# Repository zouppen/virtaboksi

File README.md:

# Virtaboksi

Virtaboksi is a multi-purpose 3-channel common-earth power switch,
rating 12–48 VDC, 20 A. It has multiple operating modes:

* **Home/away switch** supporting three individual groups and is optimized
  for solar energy off-grid applications.

* **Water pump controller** with pressure sensor input and control for
  combined submersible and pressure pump system. Additionally, a
  throw-over switching capability to drop loads while pumping.

* Generic **Modbus RTU server** (slave) with 3 solid-state "coils", 3 digital
  outputs, and 4 digital inputs.

In the picture above the Powerpole connector colors are incorrect. Red
is used for inputs and black for outputs. In a real product, the three
groups have different colors: red, yellow and blue.

## Design principles

* **Flexible voltage** options; 10–34 V input on first group, 10–60 V on
  second and third group.
* **High current** support. With passive cooling, 20 A loads can be
  controlled. MOSFETs are capable of switching over 100 A continuous
  current in case where cooling and PCB traces are reinforced.
* **Small** size: Thanks to transistor control, the size is way smaller than for
  three contactors of similar rating.
* **Low losses**: Internal resistance <10mΩ.
* **Rugged**: All digital I/O ports are short-circuit, reverse voltage and
  surge protected.
* **Power saving**: When loads are off, the power consumption is minimal,
  less than 5mW, allowing it to be left powered on over dark winters.
* **Hacker friendly**: You can create your own firmware for the STM8
  microcontroller, allowing real-time and stand-alone control of your
  loads and connectivity to other peripherals up to **1 km** distance
  over RS-485.

## Operating modes

### Home/away mode

Status: 💚 **Functional**

This unit provides *priority* output on OUT1 when the switch is in
either *home* or *away* position. *Home* controls OUT2 and OUT3 groups
and can be used to control two separate voltages as long as they have
a common ground.

An example use case is a solar off-grid system with two 12V batteries
in series providing 24 volts, plus 12 volts generated from 24V using a
step-down DC converter. DC converter is not included in the package.

In that case this switch can be used to turn the loads partially while
being away, such as keeping refrigerator running but turning off
lights while not present. When using a DC converter, its input is connected
OUT1 its output (12V) to IN3.

Maximum voltage in IN1 is 34 VDC. The limitation comes from the
internal power supply. In case you want to use higher voltages in IN1,
cut the trace F1 on the bottom of this board and power the system
directly from a regulated 3.3 VDC supply via the terminals.

IN2 and IN3 are rated for 60 volts maximum, making it possible to
control 48V nominal voltage loads. Minimum voltage for all groups is
about 10 volts. Under 10 volts, MOSFET control becomes unreliable.

#### How to connect

In home/away mode, when I1 is shorted to the ground, the oprating mode
is *away*. When I2 is shorted, the mode is *home*. If both connectors
are open, operating mode is *off*.

Optionally, LED anodes can be connected directly to O1 and O2. They
represent home and away operating modes, in that order. There is a
current limiter controllable by R1 to limit the maximum current of
O1...O3 to about 15 mA by default, so series resistors are not needed.

If your solar controller has a low battery condition relay, it can be
connected to I3. When the input is high, the system is forced to off mode,
ignoring the state of home/away switch.

I4 is not used in this mode.

### Water pump controller mode

Status: 🔬 **Hardware OK**

Hardware is capable, but no firmware support yet.

### Modbus RTU server mode

Status: 🔬 **Hardware OK**

RS-485 hardware is tested and some firmware tests performed, but no
Modbus implementation exists yet.

## Building firmware

To build firmware, you need CMake and sdcc. The preparations are very
standard CMake stuff. In `firmware` subdirectory, run:

```sh
mkdir build
cd build
cmake ..
```

And then, `make` compiles it. Alternatively, `make upload` to compile
and flash.

## License

The firmware is free software: you can redistribute it and/or modify
it under the terms of the GNU Affero General Public License as
published by the Free Software Foundation, either version 3 of the
License, or (at your option) any later version.

The hardware is provided as source-available: The schematics and PCB
layout are provided for reference only. The files can be freely
distributed without limitations but no derivative works are allowed
without a permission from the copyright holders.

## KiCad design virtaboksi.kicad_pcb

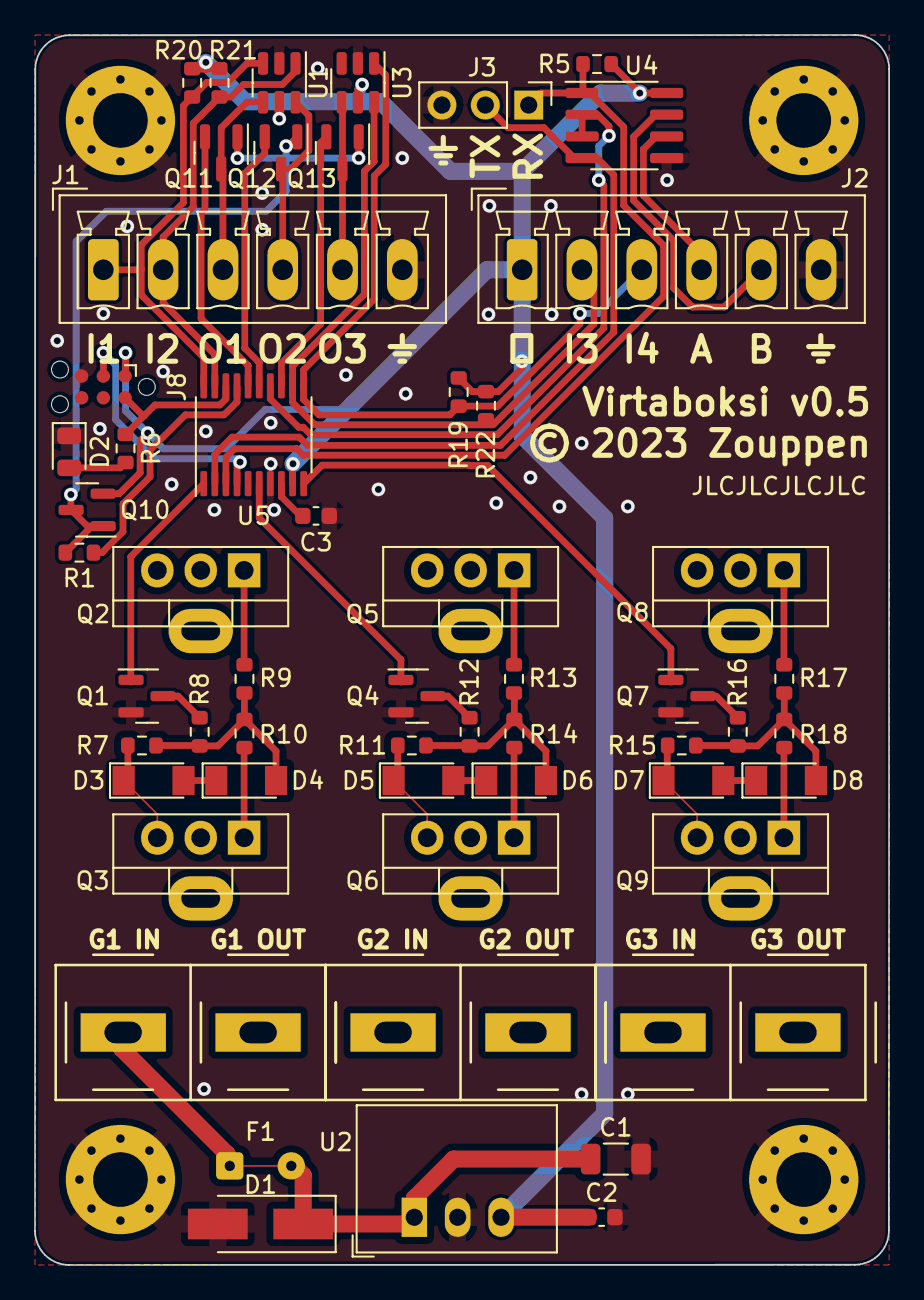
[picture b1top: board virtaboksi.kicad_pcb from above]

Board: 2 copper layers, 50.0 x 72.0 mm, 66 parts (0 on the bottom side), 48 nets.

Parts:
C1: 10u; C_1206_3216Metric
C2: 22u; C_0603_1608Metric
C3: 1u; C_0603_1608Metric
D1: SMAJ33A; D_SMA_Handsoldering
D2: LED; LED_0805_2012Metric
D3, D4, D5, D6, D7, D8: ZMM5V6-M; D_MiniMELF
F1: Fuse; Fuse-kindof_1x02_P3.6mm_D0.4mm_OD1mm
H1, H2, H3, H4: MountingHole_Pad; MountingHole_3.2mm_M3_Pad_Via
HS1, HS2, HS3, HS4, HS5, HS6: Heatsink; Heatsink_AAVID_576802B03900G-nocourt
J1: Panel_01x06; PhoenixContact_MCV_1,5_6-G-3.5_1x06_P3.50mm_Vertical
J2: External_01x06; PhoenixContact_MCV_1,5_6-G-3.5_1x06_P3.50mm_Vertical
J3: Optional_01x03; PinHeader_1x03_P2.54mm_Vertical
J5, J6, J7: Powerpole 01x02; 45A-VERT-PAIR
J8: TagConnect_TC2030-NL; Tag-Connect_TC2030-IDC-NL_2x03_P1.27mm_Vertical
Q1, Q4, Q7: 2N7002; SOT-23
Q2, Q3, Q5, Q6, Q8, Q9: IRF4905; TO-220-3_Vertical
Q10, Q11, Q12, Q13: MMBT3906; SOT-23
R1, R6: 220; R_0603_1608Metric
R5: 20k; R_0603_1608Metric
R7, R11, R15: 68k; R_0603_1608Metric
R8, R12, R16: 13k; R_0603_1608Metric
R9, R10, R13, R14, R17, R18: 10; R_0603_1608Metric
R19, R20, R21, R22: 5k; R_0603_1608Metric
U1, U3: SRV05-4; SOT-23-6
U2: AMSRI-783.3-NZ; Converter_DCDC_RECOM_R-78E-0.5_THT
U4: SP3485EN; SOIC-8_3.9x4.9mm_P1.27mm
U5: STM8S003F3P; TSSOP-20_4.4x6.5mm_P0.65mm

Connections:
+3.3V: C2.1, J2.1, J8.1 (VCC), Q10.2 (E), R5.1, R19.1, R20.1, R21.1, R22.1, U1.5 (VP), U2.3 (OUT), U3.5 (VP), U4.8 (VCC), U5.9 (VDD)
/GROUP1 CTRL: Q1.1 (G), U5.1 (PD4)
/GROUP1 IN: D3.1 (K), F1.1, J7.2, Q2.3 (S), Q3.3 (S), R7.1
/GROUP1 OUT: HS1.1, HS2.1, J7.1, Q2.2 (D), Q3.2 (D)
/GROUP2 CTRL: Q4.1 (G), U5.6 (PA2)
/GROUP2 IN: D5.1 (K), J6.2, Q5.3 (S), Q6.3 (S), R11.1
/GROUP2 OUT: HS3.1, HS4.1, J6.1, Q5.2 (D), Q6.2 (D)
/GROUP3 CTRL: Q7.1 (G), U5.10 (PA3)
/GROUP3 IN: D7.1 (K), J5.2, Q8.3 (S), Q9.3 (S), R15.1
/GROUP3 OUT: HS5.1, HS6.1, J5.1, Q8.2 (D), Q9.2 (D)
/IN1: J1.1, R20.2, U1.3 (IO2), U5.20 (PD3)
/IN2: J1.2, R21.2, U1.1 (IO1), U5.19 (PD2)
/IN3: J2.2, R22.2, U3.6 (IO4), U5.12 (PB4)
/IN4: J2.3, R19.2, U3.1 (IO1), U5.11 (PB5)
/IREF: Q10.1 (B), Q10.3 (C), Q11.1 (B), Q12.1 (B), Q13.1 (B), R1.1
/IREF_EN: R1.2, U5.17 (PC7)
/O1: J1.3, Q11.3 (C), U1.4 (IO3)
/O1uC: Q11.2 (E), U5.16 (PC6)
/O2: J1.4, Q12.3 (C), U1.6 (IO4)
/O2uC: Q12.2 (E), U5.15 (PC5)
/O3: J1.5, Q13.3 (C), U3.4 (IO3)
/O3uC: Q13.2 (E), U5.13 (PC3)
/PWR1: C1.1, D1.1 (A1), F1.2, U2.1 (IN)
/RESET: J8.3 (~RESET), U5.4 (NRST)
/RX: J3.1, R5.2, U4.1 (RO), U5.3 (PD6)
/SWIM: J8.2 (SWDIO), R6.2, U5.18 (PD1)
/TX: J3.2, U4.4 (DI), U5.2 (PD5)
/TX_EN: U4.2 (~RE), U4.3 (DE), U5.14 (PC4)
/mosfet_switch1/DRIVE: D4.2 (A), R7.2, R8.1, R9.1, R10.1
/mosfet_switch1/DRIVE_A: Q2.1 (G), R9.2
/mosfet_switch1/DRIVE_B: Q3.1 (G), R10.2
/mosfet_switch2/DRIVE: D6.2 (A), R11.2, R12.1, R13.1, R14.1
/mosfet_switch2/DRIVE_A: Q5.1 (G), R13.2
/mosfet_switch2/DRIVE_B: Q6.1 (G), R14.2
/mosfet_switch3/DRIVE: D8.2 (A), R15.2, R16.1, R17.1, R18.1
/mosfet_switch3/DRIVE_A: Q8.1 (G), R17.2
/mosfet_switch3/DRIVE_B: Q9.1 (G), R18.2
A: J2.4, U4.6 (A)
B: J2.5, U4.7 (B)
GND: C1.2, C2.2, C3.2, D1.2 (A2), D2.1 (K), H1.1, H2.1, H3.1, H4.1, J1.6, J2.6, J3.3, J8.5 (GND), Q1.2 (S), Q4.2 (S), Q7.2 (S), U1.2 (VN), U2.2 (GND), U3.2 (VN), U4.5 (GND), U5.7 (VSS)
unnamed: C3.1, U5.8 (VCAP)
unnamed: D2.2 (A), R6.1
unnamed: D3.2 (A), D4.1 (K)
unnamed: D5.2 (A), D6.1 (K)
unnamed: D7.2 (A), D8.1 (K)
unnamed: Q1.3 (D), R8.2
unnamed: Q4.3 (D), R12.2
unnamed: Q7.3 (D), R16.2

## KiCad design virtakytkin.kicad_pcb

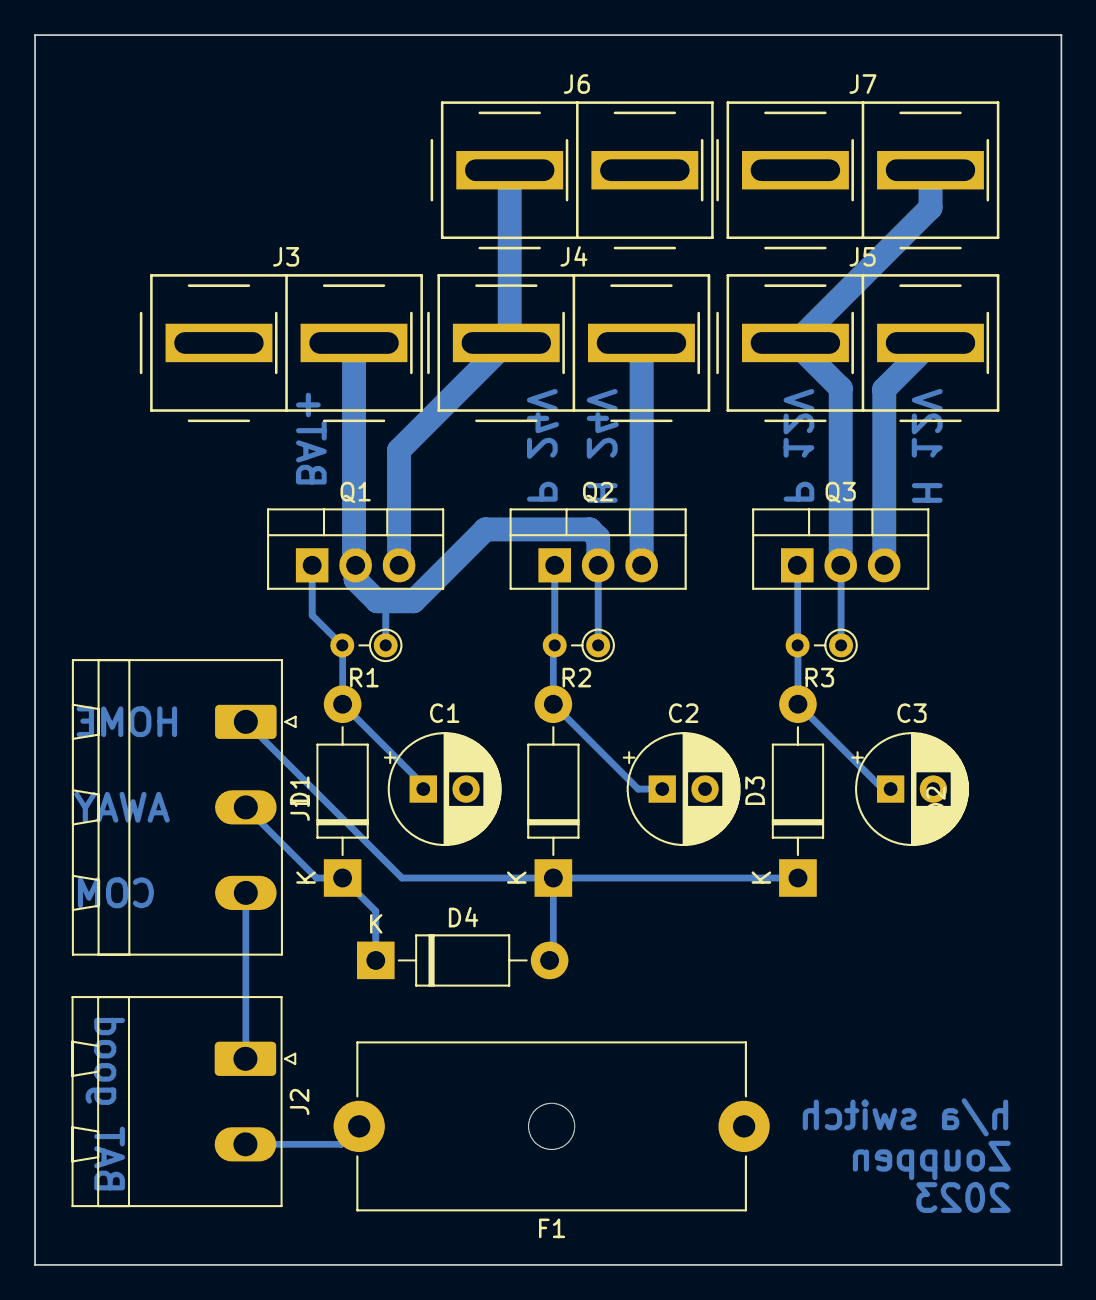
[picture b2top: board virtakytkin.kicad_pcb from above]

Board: 2 copper layers, 60.0 x 71.9 mm, 21 parts (0 on the bottom side), 13 nets.

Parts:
C1, C2, C3: C_Polarized; CP_Radial_D6.3mm_P2.50mm
D1, D2, D3, D4: 1N4001; D_DO-41_SOD81_P10.16mm_Horizontal
F1: Fuse; Fuseholder_Cylinder-5x20mm_Schurter_0031_8201_Horizontal_Op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
J1: Conn_01x03_Female; PhoenixContact_MSTBA_2,5_3-G_1x03_P5.00mm_Horizontal
J2: Conn_01x02_Female; PhoenixContact_MSTBA_2,5_2-G_1x02_P5.00mm_Horizontal
J3, J4, J5, J6, J7: Conn_01x02_Female; 45A-VERT-PAIR
Q1, Q2, Q3: IRF9540N; TO-220-3_Vertical
R1, R2, R3: 100k; R_Axial_DIN0204_L3.6mm_D1.6mm_P2.54mm_Vertical

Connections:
+BATT: J3.2, Q1.2 (D), Q2.2 (D), R1.1, R2.1
/AWAY: D1.1 (K), D4.1 (K), J1.2
/BAT GOOD: J1.3, J2.1
/HOME: D2.1 (K), D3.1 (K), D4.2 (A), J1.1
/HOME 12V: J5.2, Q3.3 (S)
/HOME 24V: J4.2, Q2.3 (S)
/PRI 12V: J5.1, J7.2, Q3.2 (D), R3.1
/PRI 24V: J4.1, J6.1, Q1.3 (S)
GND: C1.2, C2.2, C3.2, F1.1, J3.1, J6.2, J7.1
unnamed: C1.1, D1.2 (A), Q1.1 (G), R1.2
unnamed: C2.1, D2.2 (A), Q2.1 (G), R2.2
unnamed: C3.1, D3.2 (A), Q3.1 (G), R3.2
unnamed: F1.2, J2.2

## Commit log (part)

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2016-09-14 First version
2023-07-06 Add license
2023-07-06 Add current version of the project
2023-07-06 Rename project
2023-07-06 Add submodule for Powerpole connectors
2023-07-06 Move powerpoles so that they are stackable
2023-07-06 Finetuning layout & adding TVS diode
2023-07-17 MOSFET drain and source were flipped
2023-07-17 Run the thing in Falstad's simulator and adjust the circuit
2023-07-18 Change caps from elco to ceramic, reannotate
2023-07-18 Move overvoltage protection diode down, center DC converter pins
2023-07-18 Remove grounding pins for DC converter
2023-07-18 Add gerber export directory
2023-07-18 Add circuitjs simulation of this circuit
2023-07-19 Add image
2023-07-19 Add principle of operation to README
2023-07-22 Make schematics more readable, no functional changes
2023-07-28 Add origin point to the PCB
2023-07-29 Get rid of warnings, make TagConnect region more beautiful
2023-07-29 Rename power labels
2023-07-29 Update PCB labels to more understandable ones
2023-07-29 Add more capacitance to DC converter output, add DC output pins, minor cleanup
2023-07-29 Make voltage planes larger and remove solder mask from there
2023-07-29 Change TVS diode type to 33.3V
    This is to avoid TVS breakdown during solar charge controller
    equalization charge which uses higher voltages (up to 32 volts). The
    regulator type is updated to the one we plan to use (36V version).
2023-07-30 Heavily refactor board layout
2023-07-30 Make it pass DRC
2023-07-30 Making some small changes to improve ground connections
2023-07-30 Voltage plane redraw
2023-07-30 Fixes suggested by DRC
2023-07-30 Small improvements
    - Add extra single pin for debugging microcontroller code
    - Add vias to screw holes
2023-07-30 Release v0.2
2023-07-30 Add simulation with two MOSFETs, the current version
2023-08-10 Somewhat working logic with sleep mode
2023-08-10 Move control logic to a function which is run after debouncing
2023-08-10 Pin configuration and structure
2023-08-10 Add control logic
2023-08-11 Move firmware files to firmware directory
2023-08-16 Finished version 0.3, ready for prototype production
2023-08-16 Just fork hw0.2 -> hw0.3, no changes yet
2023-08-16 Fix indent and comments. Make volatile var volatile
2023-08-16 Minor cleanup in Makefile
2023-08-16 Fix old labels on the silkscreen
2023-08-17 Update README a bit
2023-08-17 Typofix
2023-08-17 Updated connectors, causing large diff of nothing
2023-09-05 Invert SW_BAT to be NC instead of NO. Reduce debounce to 100ms.
2023-09-17 Update transistor numbers in schematic text
2023-09-17 Group heatsinks to one place on the schematics
2023-09-17 And rename control lines as well
2023-09-17 Minor schematic tidying
2023-09-25 Connect v0.4 components
2023-09-25 Small adjustments to the references and such
2023-09-25 Add 2.54mm pin header for RX/TX to ease debugging
2023-09-25 Trace width adjustment
2023-09-25 Forgot to add the mosfet module sheet
2023-09-26 Minor cosmetic PCB changes
2023-09-26 Update solder mask, do final tweaks, make it pass ERC & DRC
2023-09-26 Reannotate everything
2023-09-27 Throw fuse out of the window, clear space left of J2, add 2 extra pins
2023-09-27 Add makeshift fuse
2023-09-28 Add stronger pull-ups for inputs
2023-09-28 Move one input to external connector, make them same length
2023-09-28 Rename nets to be more intuitive
2023-09-28 And finally J2 label on board
2023-10-02 Probably final changes before v0.4 production
2023-10-02 Final changes before production
2023-10-05 Remove extra E1 and E2 labels, that connector is removed already
2023-10-05 Flip TX_EN1 and TX_EN2, reroute PCB a bit
2023-10-06 Adjust component and trace placement to make screw positions nice
2023-10-06 Move TC2030 connector so that it's not blocked by heat shield
2023-10-06 Swap J1 and J2 and move vias a little
2023-10-06 Tune traces near CPU
2023-10-07 Final tweaks to the PCB. Swap LED pins for better routing.
2023-10-09 Ignore gerbers subdirectory for now
2023-10-09 firmware: Start firmware by duplicating v0.3
2023-10-09 Update label text in subsheet
2023-10-09 firmware: Update pins to match hw0.4
2023-10-09 Rename HOME voltage markings with generic 1 and 2
2023-10-09 Move SMD LED so that it's not blocked by a heat sink
2023-10-09 firmware: reorganize macros and constants
2023-10-09 firmware: Fix stm8flash parameters and verify, too
2023-10-10 Evacuate output from PA1, not working with halt mode
2023-10-11 Reverse LED logic to drive low and switch pins to match my test hardware
2023-10-12 Add current mirror, rename traces
2023-10-12 Approach version 0.5. Let it cool down for day or two.
2023-10-12 Remove one unnecessary via
2023-10-12 Switch to 220 ohm resistor to generate 15 mA
2023-10-12 Move labels, change on-board LED resistor from 180 ohm to 220
2023-10-12 Move AIN4 pin to IN2 to make it possible to use it for analog in the future
2023-10-12 Add a label mentioning about analog use
2023-10-12 Trace and via adjustment
2023-10-12 Rounded corners. This is important!
2023-10-13 Refill areas
2023-10-13 Incorrect part number spotted before production, 1.5kohm -> 4.7kohm
2023-10-13 Make clearance larger for power lines and relief smaller for ground (both now 0.4mm)
2023-10-13 Move capacitors so that traces make up direct lines
2023-10-13 Explain home/away operating mode
2023-10-13 Rephrase README
2023-10-13 Design principles
2023-10-13 Sales pitch
2023-10-13 Better word in README
2023-10-13 Bold and beautiful readme
2023-10-13 Readme: rephrase
2023-10-13 Readme: Change subtitles
2023-10-13 Power saving target to README
2023-10-13 Change bidirectional TVS to unidirectional
2023-10-13 Add JLCPCB order number to a predefined spot
2023-10-13 Rename IN1..3 as Gn IN and OUT1..3 Gn OUT on silkscreen
2023-10-14 Mosfet drive clearances larger, update comments
2023-10-14 Minor tweak: reset trace routing
2023-10-14 Readme: Add hacker friendliness
2023-10-14 Mention RS-485
2023-10-14 Mention RS-485 distance
2023-10-14 Mention about winter-friendliness
2023-10-16 Adapt AVR macros from Pumpunjuksautin
    From here https://github.com/zouppen/pumpunjuksautin
    Helps porting routines from that project, too.
2023-10-16 Description about boot loop
2023-10-16 Improve readability
2023-10-16 Clean up by removing camelCase inline asm
2023-10-16 Turn off pull-ups for inputs
2023-10-16 Hardware configuration using names we use in schematics
2023-10-16 Fix pins to match HW version 0.4
2023-10-16 Add support for UART rx
2023-10-16 Fix interrupt number and rename debounce_check better
2023-10-16 Remove whitespaces and untabify
2023-10-16 Add support for serial sleep mode (loses one character on wakeup)
2023-10-16 Move magic numbers to constants and shut down serial in case of inactivity
2023-10-16 Put the serial port to unreal mode
2023-10-17 Round baud rate to nearest integer, making bit error smaller
2023-10-17 Improve comments
2023-10-17 Make current limiter a bit more safe by making reference current sinking
2023-10-17 Add a single comment
2023-10-17 Separate initial wakeup and actual serial communications shutdown timeout
2023-10-17 Recover from halt differently, without falling out from interrupt handler
2023-10-18 Add maybe_halt() function and clean up interrupt handling
    Read PM0044. It's good stuff.
2023-10-18 Remove unnecessary if
2023-10-18 snooze_suppressor is not for serial only, changing comments & initially 0
2023-10-18 Turn off RS-485 transmitter in an interrupt when tx finished
2023-10-18 Move UART header labels to the front silkscreen
2023-10-18 Proper interrupt-driven UART comms
2023-10-18 Update comment in PORTD interrupt handler.
2023-10-18 Add ROT-13 demo for the serial traffic
2023-10-18 Safety snooze suppression in serial tx is no longer needed. Works without.
2023-10-18 Rename halt function and variable to more descriptive ones
2023-10-19 Move PIN_RX to stm8.h since it's MCU specific anyway
2023-10-19 Move pin definitions to pins.h
2023-10-19 Add board definition
    That way same firmware code can be conditionally compiled to multiple
    hw versions.
2023-10-19 Do an epic overloaded macro
    It's for pins which are from same bank but controlled together. When
    reading the value, the first pin is used.
2023-10-19 Move interruptable ports to pins.h
2023-10-19 Rename pins.h -> board.h
2023-10-19 Move UART configuration to stm8.c
2023-10-19 Clock configuration to stm8.c
2023-10-19 Move rot13 to util.c
2023-10-19 Make main.c internal functions static
2023-10-19 Handle error where no board version is defined
2023-10-19 Preliminary IREF support
2023-10-20 Make serial support arbitrary length send buffers
2023-10-21 Support new -R flag in stm8flash to reset the board after flashing
    The feature is added by
    https://github.com/vdudouyt/stm8flash/pull/168
2023-10-21 Clean TCIEN handling
2023-10-21 In initialization |= is not needed for register which are 0 on boot
2023-10-21 Use __critical instead of manual sim&rim
2023-10-22 Free PIN_OUT3 for debug use for now. It's not used in HOME/AWAY mode anyway
2023-10-22 Enforce Linux coding style
    Put main-level function start brace on a distinct line
2023-10-22 Make the timer running indicator more clearly named
2023-10-22 Move the serial idle check to the main function
2023-10-22 Concentrate serial operations in serial.c. Copy header from Pumpunjuksautin
2023-10-22 Move serial initialization to serial.c
2023-10-25 Move serial receive interrupt to serial.c
2023-10-25 Make a build-time option about enabling STM8 HALT
2023-10-25 Simplify interrupt edge setting since we use only edge setting
2023-10-25 Port E and F pull-ups are enabled even though not wired on STM8S003?3
2023-10-25 Add missing interrupt numbers for IO banks
2023-10-25 Minor comment update
2023-10-25 Fix IN3 and IN4 malfunction, interrupt was missing
2023-10-25 Simplify tick system
2023-10-25 Rename nul_terminated to tx_nul_terminated in serial.c
2023-10-26 Add serial tx double buffering. WIP, it is broken.
2023-10-29 Fix serial rx problem when BREAK occurs
    It was transmitting while receiving, which breaks half-duplex.
2023-10-29 WIP pin
2023-10-30 Cleaner double buffering handling
2023-10-30 Use _IM suffix in function names to indicate calling conditions
    _IM means interrupts must be masked (disabled) before calling that
    function. Interrupts stay disabled during the call.
2023-10-30 Volatile is not needed in ctrl_debounce and ctrl_panic
    Those are called from interrupts anyway
2023-10-30 Make loop void and add a way to query serial buffer state
2023-10-30 Use Arduino-like names for setup and loop
2023-10-30 Shorten the generated code
2023-10-30 Use the same interrupt names than lujji
    Throwing jukkas' names out of the window and replace with better ones
    from here:
    https://github.com/lujji/stm8-bare-min/blob/master/stm8s/lib/stm8s.h
2023-10-30 Migrate to _BV macro, since we have it
2023-10-30 Add EEPROM lock/unlock functions
2023-10-30 Quick & dirty optimization to avoid wear on MCU flash
    Doesn't flash the microcontroller if it already contains that code.
2023-10-31 Name pull_serial_counters properly and optimize
2023-10-31 Keep on harmonizing with stm8-bare-min
2023-10-31 Rename rim()/sim() to match with stm8-bare-min
2023-10-31 Remove legacy versions, we support only boards after 0.4 now
2023-11-01 Move upload logic out of Makefile
2023-11-01 Migrate to CMake, finally.
2023-11-01 Move baud rate and calculating of Modbus timing to CMake
2023-11-01 Make clock speed configurable in CMake
2023-11-01 CPU frequency conf in megahertz
2023-11-01 Fix Modbus silence calculation
2023-11-01 Add debug view to CMake, listing all configuration variables
2023-11-01 Simplify the silence duration calculation
2023-11-01 Baud rate must be 32-bit since there are higher baud rates than 65535
2023-11-01 Add settings module for EEPROM stored settings
2023-11-01 Make baud rate configurable
2023-11-01 Move MODBUS_SILENCE from CMake to a run-time setting
2023-11-01 Cache modbus_silence. Otherwise takes too much time to calculate it
2023-11-03 Make 16-bit timer count at pace of 1MHz, while keeping tick at 1ms
